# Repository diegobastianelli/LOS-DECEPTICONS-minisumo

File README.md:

# LOS DECEPTICONS — Robot Mini-Sumo
Robot de mini-sumo autónomo diseñado y fabricado por el equipo **LOS DECEPTICONS** para la asignatura **Tecnología Eléctrica** de la **Universidade de Santiago de Compostela (USC)**.

## Equipo

- Diego Bastianelli Lorenzo
- Rubén Célix Rodríguez
- Samuel Agrasar Magariños

## Descripción

El robot cumple la normativa estándar de mini-sumo: base de máximo 10 × 10 cm, masa máxima de 500 g y retardo obligatorio de 5 s antes de moverse. La electrónica se integra en una PCB propia de dos capas que actúa como placa base (*shield*): los módulos comerciales (microcontrolador, driver de motores y regulador) se insertan en zócalos, y los sensores se conectan por cable.

## Hardware

| Bloque | Componente |
|---|---|
| Microcontrolador | ESP32-S3 Zero (Waveshare) |
| Driver de motores | TB6612FNG (módulo dual) |
| Motores | 2 × N20 micromotorreductor 6 V, 600 RPM (tracción diferencial 2WD) |
| Batería | LiPo 2S 7.4 V, 450 mAh, 75C, conector XT30 |
| Regulador | DD4012SA, salida fija 5 V / 1 A |
| Sensores de oponente | 5 × Sharp GP2Y0A41SK0F (4–30 cm), 3 frontales y 2 laterales |
| Sensores de borde | 2 × QRE1113 (salida digital por descarga RC) |
| Selección de estrategia y arranque | DIP switch de 4 posiciones |
| Chasis | PLA impreso en 3D |
| Ruedas | Silicona |

### PCB

- Diseñada en KiCad 10, 60 × 80 mm, dos capas, FR-4 de 1.6 mm, acabado HASL.
- Divisores de tensión resistivos (10 kΩ / 20 kΩ) para adaptar la salida de los Sharp (5 V) al ADC del ESP32 (3.3 V).
- Pistas de 0.8 mm para potencia y 0.25 mm para señal; plano de masa en la capa inferior.
- Fabricada por JLCPCB. Gerbers en `hardware/gerbers/`.

## Estructura del repositorio

```
hardware/
  pcb/        Proyecto KiCad (esquemático y PCB)
  gerbers/    Archivos de fabricación
mecanica/     Diseño 3D del chasis y la pala
firmware/     Código del ESP32-S3 Zero
docs/         Ficha técnica, informe y fotos
```

## Estado del proyecto

- [x] Esquemático y PCB diseñados
- [x] PCB enviada a fabricar
- [ ] Diseño e impresión del chasis
- [ ] Montaje y soldadura
- [ ] Firmware
- [ ] Pruebas y campeonato

## Licencia

- Hardware (`hardware/`, `mecanica/`): [CERN-OHL-P v2](LICENSE)
- Firmware (`firmware/`): MIT

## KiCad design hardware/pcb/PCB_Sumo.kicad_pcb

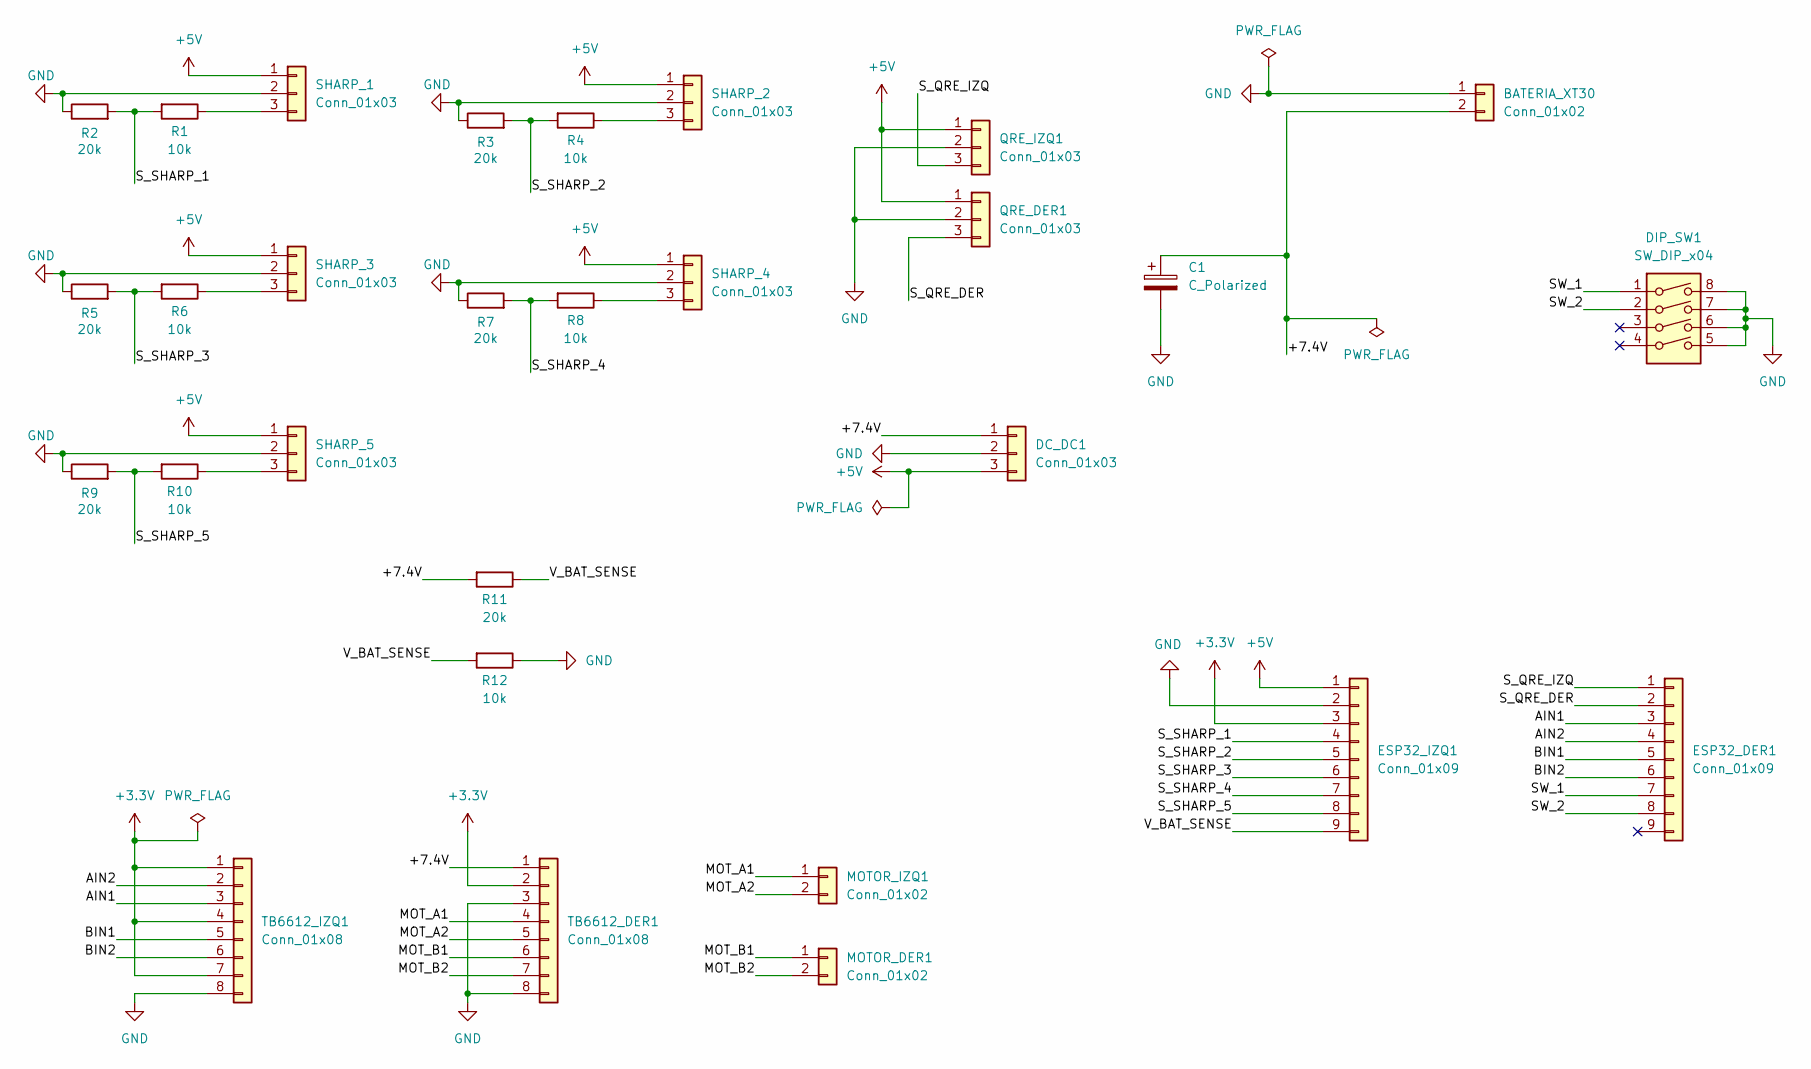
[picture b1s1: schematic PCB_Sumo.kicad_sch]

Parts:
BATERIA_XT30: Conn_01x02; PinHeader_1x02_P2.54mm_Vertical
C1: C_Polarized; CP_Radial_D5.0mm_P2.50mm
DC_DC1: Conn_01x03; PinHeader_1x03_P2.54mm_Vertical
DIP_SW1: SW_DIP_x04; SW_DIP_SPSTx04_Slide_9.78x12.34mm_W7.62mm_P2.54mm
ESP32_DER1, ESP32_IZQ1: Conn_01x09; PinSocket_1x09_P2.54mm_Vertical
MOTOR_DER1: Conn_01x02; PinHeader_1x02_P2.54mm_Vertical
MOTOR_IZQ1: Conn_01x02; PinHeader_1x02_P2.54mm_Vertical
QRE_DER1: Conn_01x03; PinHeader_1x03_P2.54mm_Vertical
QRE_IZQ1: Conn_01x03; PinHeader_1x03_P2.54mm_Vertical
R1, R4, R6, R8, R10, R12: 10k; R_Axial_DIN0207_L6.3mm_D2.5mm_P10.16mm_Horizontal
R2, R3, R5, R7, R9, R11: 20k; R_Axial_DIN0207_L6.3mm_D2.5mm_P10.16mm_Horizontal
SHARP_1, SHARP_2, SHARP_3, SHARP_4, SHARP_5: Conn_01x03; PinHeader_1x03_P2.54mm_Vertical
TB6612_DER1, TB6612_IZQ1: Conn_01x08; PinSocket_1x08_P2.54mm_Vertical

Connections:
+3.3V: ESP32_IZQ1.3, TB6612_DER1.2, TB6612_IZQ1.1, TB6612_IZQ1.4, TB6612_IZQ1.7
+5V: DC_DC1.3, ESP32_IZQ1.1, QRE_DER1.1, QRE_IZQ1.1, SHARP_1.1, SHARP_2.1, SHARP_3.1, SHARP_4.1, SHARP_5.1
/+7.4V: BATERIA_XT30.2, C1.1, DC_DC1.1, R11.2, TB6612_DER1.1
/AIN1: ESP32_DER1.3, TB6612_IZQ1.3
/AIN2: ESP32_DER1.4, TB6612_IZQ1.2
/BIN1: ESP32_DER1.5, TB6612_IZQ1.5
/BIN2: ESP32_DER1.6, TB6612_IZQ1.6
/MOT_A1: MOTOR_IZQ1.1, TB6612_DER1.4
/MOT_A2: MOTOR_IZQ1.2, TB6612_DER1.5
/MOT_B1: MOTOR_DER1.1, TB6612_DER1.6
/MOT_B2: MOTOR_DER1.2, TB6612_DER1.7
/SW_1: DIP_SW1.1, ESP32_DER1.7
/SW_2: DIP_SW1.2, ESP32_DER1.8
/S_QRE_DER: ESP32_DER1.2, QRE_DER1.3
/S_QRE_IZQ: ESP32_DER1.1, QRE_IZQ1.3
/S_SHARP_1: ESP32_IZQ1.4, R1.2, R2.2
/S_SHARP_2: ESP32_IZQ1.5, R3.2, R4.2
/S_SHARP_3: ESP32_IZQ1.6, R5.2, R6.2
/S_SHARP_4: ESP32_IZQ1.7, R7.2, R8.2
/S_SHARP_5: ESP32_IZQ1.8, R9.2, R10.2
/V_BAT_SENSE: ESP32_IZQ1.9, R11.1, R12.2
GND: BATERIA_XT30.1, C1.2, DC_DC1.2, DIP_SW1.5, DIP_SW1.6, DIP_SW1.7, DIP_SW1.8, ESP32_IZQ1.2, QRE_DER1.2, QRE_IZQ1.2, R2.1, R3.1, R5.1, R7.1, R9.1, R12.1, SHARP_1.2, SHARP_2.2, SHARP_3.2, SHARP_4.2, SHARP_5.2, TB6612_DER1.3, TB6612_DER1.8, TB6612_IZQ1.8
unnamed: R1.1, SHARP_1.3
unnamed: R4.1, SHARP_2.3
unnamed: R6.1, SHARP_3.3
unnamed: R8.1, SHARP_4.3
unnamed: R10.1, SHARP_5.3

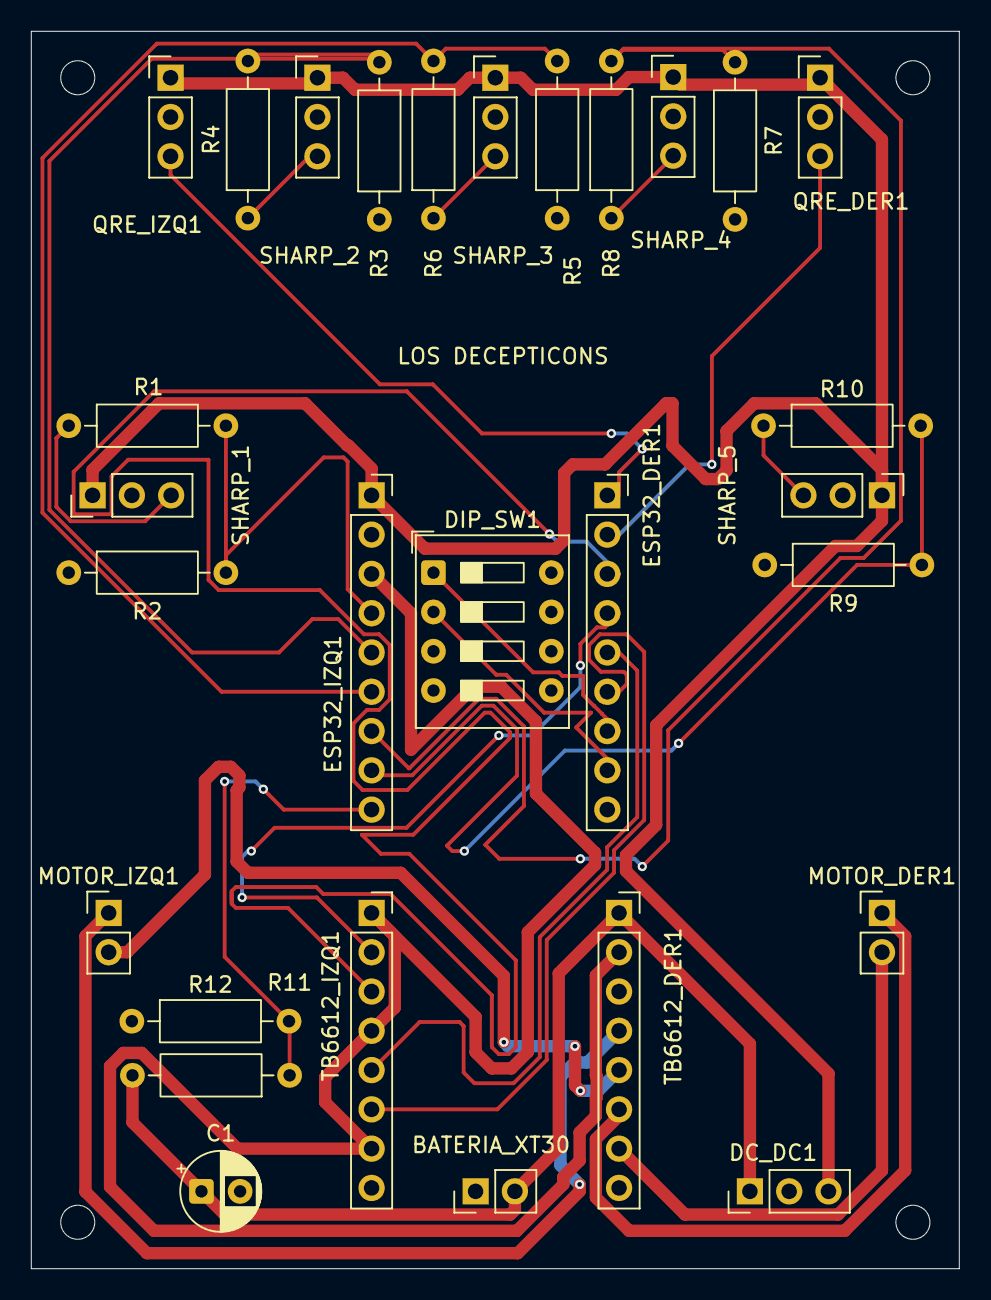
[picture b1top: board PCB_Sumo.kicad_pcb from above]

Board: 2 copper layers, 60.0 x 80.0 mm, 29 parts (0 on the bottom side), 27 nets.
